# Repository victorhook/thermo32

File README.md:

# THERMO32
This repository contains the design and source code for a smart temperature monitoring system. At it's core, the THERMO32 is a PCB which contains an [ESP32-C3](https://www.espressif.com/en/products/socs/esp32-c3) microcontroller and a [STS35](https://sensirion.com/products/catalog/STS35-DIS/) temperature sensor. The PCB comes with a USB-mini to power it, and contains a button that allows you to set it into setting-mode, where you can configure the settings through its web interface.

## Startup
When the device boots, it loads the settings and tries to connect to a WiFi with the stored WiFi SSID and password. If the device fails to connect to a WiFi within a given amount of time, it starts as an access point instead, and starts the server mode (see below) which you can connect to and configure its settings.

## Server mode
When the device is in server mode you can configure the settings.

The device can enter server mode in two ways:
1. If it fails to connect to the WiFi SSID in its configuration.
2. By holding down the button while you power on the device.

Once the device is in server mode, you can configure its settings through its webserver that you can access on port 80.

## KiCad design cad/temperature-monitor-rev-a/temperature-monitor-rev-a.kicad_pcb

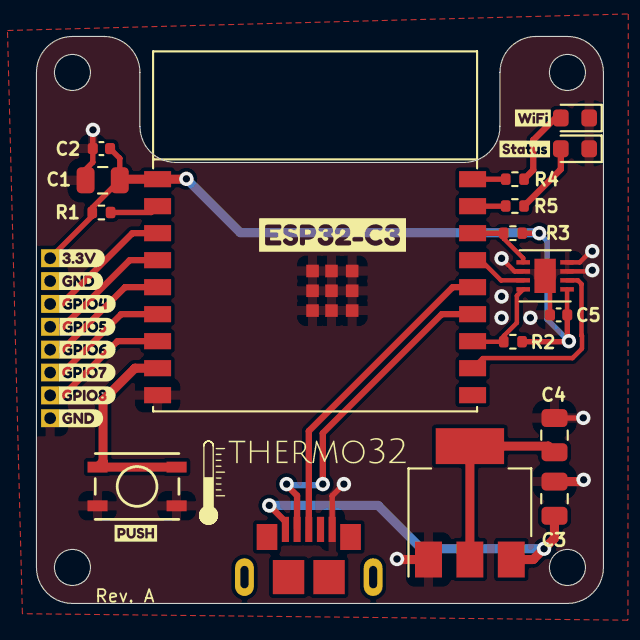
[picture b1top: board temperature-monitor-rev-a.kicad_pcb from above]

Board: 2 copper layers, 31.5 x 31.5 mm, 30 parts (0 on the bottom side), 21 nets.

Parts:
C1, C3, C4: 10uF; C_0805_2012Metric
C2: 1uF; C_0402_1005Metric
C5: 100nF; C_0402_1005Metric
D1, D2: LED; LED_0603_1608Metric
J1: USB3075-30-A; USB3075-30-A_No_silk
J2: Conn_01x08; PinHeader_1x08_P1.27mm_Vertical_No_silk
R1: 10k; R_0402_1005Metric
R2, R3: 2.2k; R_0402_1005Metric
R4, R5: 330; R_0402_1005Metric
SW1: BOOT; PTS815
U1: ESP32-C3-WROOM-02
U2: AMS1117-3.3; SOT-223-3_TabPin2
U3: STS35-DIS; STS35-DIS_temp_sensor
kibuzzard-63BBD8F6: G***; kibuzzard-63BBD8F6
kibuzzard-63BBD915: G***; kibuzzard-63BBD915
kibuzzard-63BBDC2F: G***; kibuzzard-63BBDC2F
kibuzzard-63BBE3A0: G***; kibuzzard-63BBE3A0
kibuzzard-63BBE3A5: G***; kibuzzard-63BBE3A5
kibuzzard-63BBE3D2: G***; kibuzzard-63BBE3D2
kibuzzard-63BBE32B, kibuzzard-63BBE32B#2: G***; kibuzzard-63BBE32B
kibuzzard-63BBE39B: G***; kibuzzard-63BBE39B
kibuzzard-63BBE312: G***; kibuzzard-63BBE312
kibuzzard-63BBE366: G***; kibuzzard-63BBE366
kibuzzard-63BBE393: G***; kibuzzard-63BBE393

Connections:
+3.3V: C1.1, C2.1, C5.1, J2.1, R1.1, R2.1, R3.1, U1.1 (3V3), U3.5 (VDD)
+3V3: C4.1, U2.2 (VO)
/BUTTON: SW1.1, SW1.2, U1.8 (GPIO9)
/GPIO4: J2.3, U1.3 (GPIO4/ADC1_CH4)
/GPIO5: J2.4, U1.4 (GPIO5/ADC2_CH0)
/GPIO6: J2.5, U1.5 (GPIO6)
/GPIO7: J2.6, U1.6 (GPIO7)
/GPIO8: J2.7, U1.7 (GPIO8)
/LED_BLUE: R4.2, U1.18 (GPIO0/ADC1_CH0/XTAL_32K_P)
/LED_RED: R5.2, U1.17 (GPIO1/ADC1_CH1/XTAL_32K_N)
/SCL: R2.2, U1.12 (GPIO21/U0TXD), U3.4 (SCL)
/SDA: R3.2, U1.16 (GPIO2/ADC1_CH2), U3.1 (SDA)
/TEMP_ALERT: U1.15 (GPIO3/ADC1_CH3), U3.3 (ALERT)
/TEMP_NRESET: U1.11 (GPIO20/U0RXD), U3.6 (NRESET)
/USB+: J1.3 (D+), U1.14 (GPIO19/USB_D+)
/USB-: J1.2 (D-), U1.13 (GPIO18/USB_D-)
GND: C1.2, C2.2, C3.2, C4.2, C5.2, D1.1 (K), D2.1 (K), J1.5 (GND), J2.2, J2.8, SW1.3 (K), SW1.4 (A), U1.9 (GND), U1.19 (GND), U2.1 (GND), U3.2 (ADDR), U3.7 (R), U3.8 (VSS), U3.9 (VSS)
unnamed: C3.1, J1.1 (VBUS), U2.3 (VI)
unnamed: D1.2 (A), R4.1
unnamed: D2.2 (A), R5.1
unnamed: R1.2, U1.2 (EN/CHIP_PU)

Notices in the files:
parts and their libraries:
Copyright 2016 Accelerated Designs. All rights reserved.
